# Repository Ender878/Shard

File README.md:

# Shard - Custom ESP32 S3 Board :electron:

**Shard** is an open source **ESP32 S3** board that I designed as a summer project to learn more about electronics and PCB design.

## Core features:

- 16MB Flash
- WiFi and Bluethoot capabilities
- Built-in Neopixel RGB LED
- 21 configurable GPIO pins
- Up to 16V for external Power supply
- UART & Configurable SPI and I2C pins

The board itself is pretty small, 4.6x4.8cm and doesn't have mounting holes unfortunately. It is designed to be an all-feature development board for prototyping.

## Programming

### Uploading

The board doesn't come with a **USB-UART bridge**, so the firmware uploading requires user input:

- When the uploading process starts, hold the **RESET** button
- Immediately after you pressed it, press the **BOOT** button and then release the **RESET** button
- After the code is uploaded, press the **RESET** button again to exit Download Mode, so that the board can execute the code.

### Programming with Arduino IDE 2

To program this board with the **Arduino IDE**, you have to:
- Install the "esp32" board manager.
- then select the **UM-PROS3** board 
- when uploading, follow the steps listed in the **[Uploading](#uploading)** section.

### Programming with PlatformIO (recommended)

To program this board with **PlatformIO**, you should configure the **platformio.ini** file as follows:

~~~ini
[env:esp32-s3-devkitc-1]
platform = espressif32
board = shard
framework = arduino
~~~

I made a custom **board** config file for PlatformIO that specifies all the board's specifications. To use it, create a folder called **boards** and copy [this file](./shard.json) under it.

Also, this is the partition I used:

~~~csv
# Name,   Type, SubType, Offset,  Size, Flags
nvs,      data, nvs,     0x9000,  0x5000,
otadata,  data, ota,     0xe000,  0x2000,
app0,     app,  ota_0,   0x10000, 0x700000,
app1,     app,  ota_1,   0x710000,0x700000,
spiffs,   data, spiffs,  0xe10000,0x1F0000,
~~~

PlatformIO should find the board automatically. When uploading, still follow the steps in the **[Uploading](#uploading)** section.

## Reference

To design this board, I mainly referred to the Espressif's [ESP32-S3 Hardware Design Guidelines](https://docs.espressif.com/projects/esp-hardware-design-guidelines/en/latest/esp32s3/esp-hardware-design-guidelines-en-master-esp32s3.pdf).

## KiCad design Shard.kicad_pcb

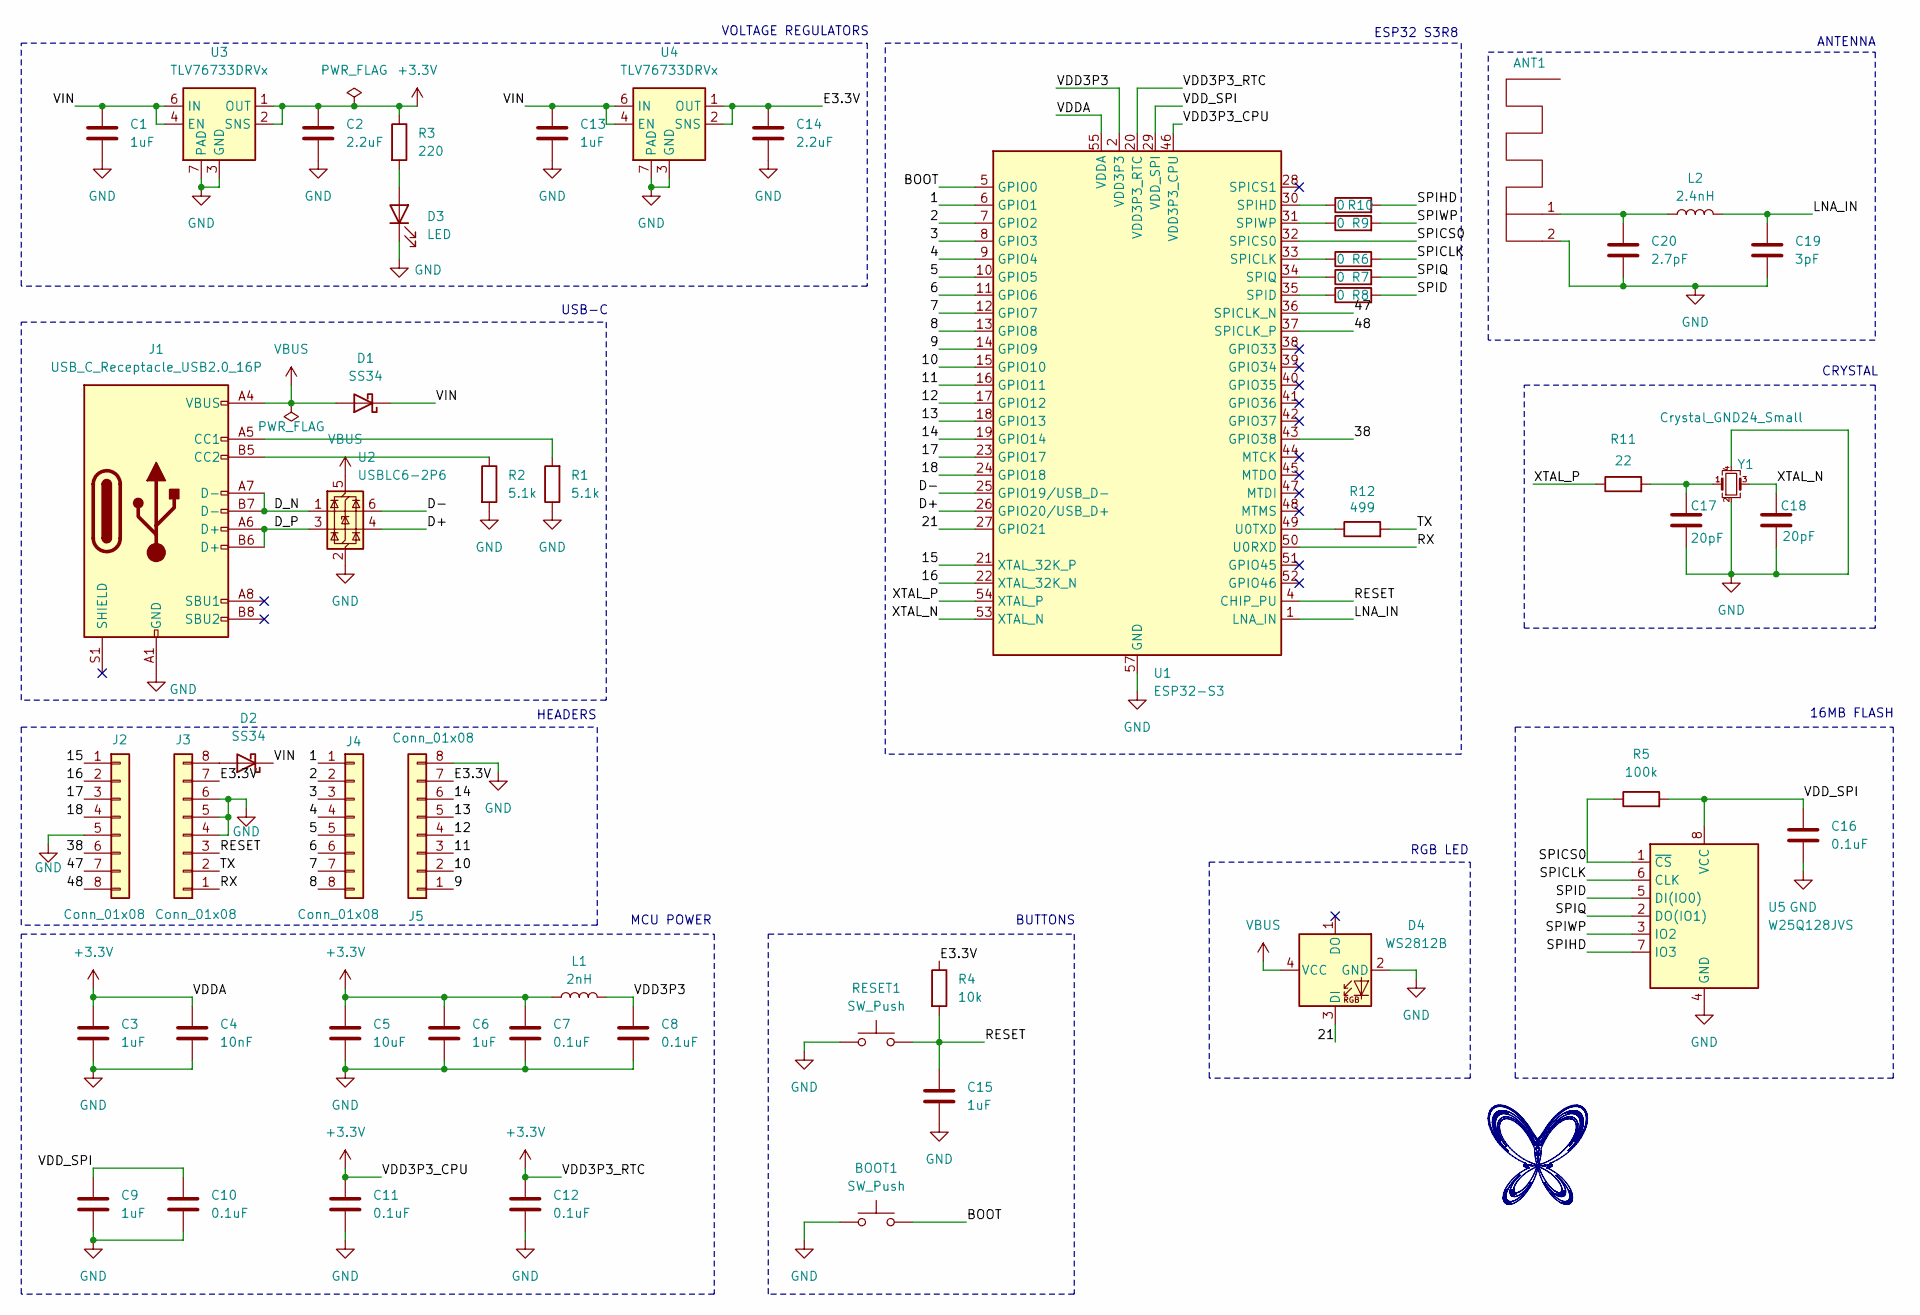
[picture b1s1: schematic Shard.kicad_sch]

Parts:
ANT1: Texas_SWRA117D_2.4GHz_Right
BOOT1: SW_Push; SW_Push_SPST_NO_Alps_SKRK
C1, C3, C9, C13, C15: 1uF; C_0201_0603Metric
C2, C14: 2.2uF; C_0402_1005Metric
C4: 10nF; C_0201_0603Metric
C5: 10uF; C_0805_2012Metric
C6: 1uF; C_0402_1005Metric
C7, C8: 0.1uF; C_0402_1005Metric
C10, C11, C12, C16: 0.1uF; C_0201_0603Metric
C17, C18: 20pF; C_0201_0603Metric
C19: 3pF; C_0201_0603Metric
C20: 2.7pF; C_0402_1005Metric
D1, D2: SS34; D_SMA
D3: LED; LED_0805_2012Metric
D4: WS2812B; LED_WS2812B-2020_PLCC4_2.0x2.0mm
J1: USB_C_Receptacle_USB2.0_16P; USB_C_Receptacle_GCT_USB4105-xx-A_16P_TopMnt_Horizontal
J2, J3, J4, J5: Conn_01x08; PinSocket_1x08_P2.54mm_Vertical
L1: 2nH; L_0201_0603Metric
L2: 2.4nH; L_0201_0603Metric
R1, R2: 5.1k; R_0402_1005Metric
R3: 220; R_0805_2012Metric
R4: 10k; R_0402_1005Metric
R5: 100k; R_1210_3225Metric
R6, R7, R8, R9, R10: 0; R_0201_0603Metric
R11: 22; R_0201_0603Metric
R12: 499; R_0805_2012Metric
RESET1: SW_Push; SW_Push_SPST_NO_Alps_SKRK
U1: ESP32-S3; QFN-56-1EP_7x7mm_P0.4mm_EP4x4mm
U2: USBLC6-2P6; SOT-666
U3, U4: TLV76733DRVx; WSON-6-1EP_2x2mm_P0.65mm_EP1x1.6mm_ThermalVias
U5: W25Q128JVS; SOIC-8_5.23x5.23mm_P1.27mm
Y1: Crystal_GND24_Small; Crystal_SMD_2520-4Pin_2.5x2.0mm

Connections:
+3.3V: C2.1, C3.1, C4.1, C5.1, C6.1, C7.1, C11.1, C12.1, L1.1, R3.1, U1.20 (VDD3P3_RTC), U1.46 (VDD3P3_CPU), U1.55 (VDDA), U1.56 (VDDA), U3.1 (OUT), U3.2 (SNS)
/1: J4.1, U1.6 (GPIO1)
/2: J4.2, U1.7 (GPIO2)
/3: J4.3, U1.8 (GPIO3)
/4: J4.4, U1.9 (GPIO4)
/5: J4.5, U1.10 (GPIO5)
/6: J4.6, U1.11 (GPIO6)
/7: J4.7, U1.12 (GPIO7)
/8: J4.8, U1.13 (GPIO8)
/9: J5.1, U1.14 (GPIO9)
/10: J5.2, U1.15 (GPIO10)
/11: J5.3, U1.16 (GPIO11)
/12: J5.4, U1.17 (GPIO12)
/13: J5.5, U1.18 (GPIO13)
/14: J5.6, U1.19 (GPIO14)
/15: J2.1, U1.21 (XTAL_32K_P)
/16: J2.2, U1.22 (XTAL_32K_N)
/17: J2.3, U1.23 (GPIO17)
/18: J2.4, U1.24 (GPIO18)
/21: D4.3 (DI), U1.27 (GPIO21)
/38: J2.6, U1.43 (GPIO38)
/47: J2.7, U1.36 (SPICLK_N)
/48: J2.8, U1.37 (SPICLK_P)
/BOOT: BOOT1.2, U1.5 (GPIO0); also elsewhere on the board
/D+: U1.26 (GPIO20/USB_D+), U2.4 (I/O2)
/D-: U1.25 (GPIO19/USB_D-), U2.6 (I/O1)
/D_N: J1.A7 (D-), J1.B7 (D-), U2.1 (I/O1)
/D_P: J1.A6 (D+), J1.B6 (D+), U2.3 (I/O2)
/E3.3V: C14.1, J3.7, J5.7, R4.1, U4.1 (OUT), U4.2 (SNS)
/LNA_IN: C19.1, L2.2, U1.1 (LNA_IN)
/RESET: C15.1, J3.3, R4.2, RESET1.2, U1.4 (CHIP_PU); also elsewhere on the board
/RX: J3.1, U1.50 (U0RXD)
/SPICLK: R6.2, U5.6 (CLK)
/SPICS0: R5.1, U1.32 (SPICS0), U5.1 (~CS)
/SPID: R8.2, U5.5 (DI(IO0))
/SPIHD: R10.2, U5.7 (IO3)
/SPIQ: R7.2, U5.2 (DO(IO1))
/SPIWP: R9.2, U5.3 (IO2)
/TX: J3.2, R12.2
/VDD3P3: C8.1, L1.2, U1.2 (VDD3P3), U1.3 (VDD3P3)
/VDD_SPI: C9.1, C10.1, C16.1, R5.2, U1.29 (VDD_SPI), U5.8 (VCC)
/VIN: C1.1, C13.1, D1.1 (K), D2.1 (K), U3.4 (EN), U3.6 (IN), U4.4 (EN), U4.6 (IN)
/XTAL_N: C18.1, U1.53 (XTAL_N), Y1.3
/XTAL_P: R11.1, U1.54 (XTAL_P)
GND: ANT1.2, BOOT1.1, C1.2, C2.2, C3.2, C4.2, C5.2, C6.2, C7.2, C8.2, C9.2, C10.2, C11.2, C12.2, C13.2, C14.2, C15.2, C16.2, C17.2, C18.2, C19.2, C20.2, D3.1 (K), D4.2 (GND), J1.A1 (GND), J1.A12 (GND), J1.B1 (GND), J1.B12 (GND), J2.5, J3.4, J3.5, J3.6, J5.8, R1.1, R2.2, RESET1.1, U1.57 (GND), U2.2 (GND), U3.3 (GND), U3.5 (GND), U3.7 (PAD), U4.3 (GND), U4.5 (GND), U4.7 (PAD), U5.4 (GND), Y1.2, Y1.4; also elsewhere on the board
unnamed: ANT1.1, C20.1, L2.1
unnamed: C17.1, R11.2, Y1.1
unnamed: D2.2 (A), J3.8
unnamed: D3.2 (A), R3.2
unnamed: J1.A5 (CC1), R1.2
unnamed: J1.B5 (CC2), R2.1
unnamed: R6.1, U1.33 (SPICLK)
unnamed: R8.1, U1.35 (SPID)
unnamed: R10.1, U1.30 (SPIHD)
unnamed: R7.1, U1.34 (SPIQ)
unnamed: R9.1, U1.31 (SPIWP)
unnamed: R12.1, U1.49 (U0TXD)
VBUS: D1.2 (A), D4.4 (VCC), J1.A4 (VBUS), J1.A9 (VBUS), J1.B4 (VBUS), J1.B9 (VBUS), U2.5 (VBUS)

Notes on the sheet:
CRYSTAL
HEADERS
MCU POWER
16MB FLASH
ANTENNA
USB-C
RGB LED
ESP32 S3R8
BUTTONS
VOLTAGE REGULATORS

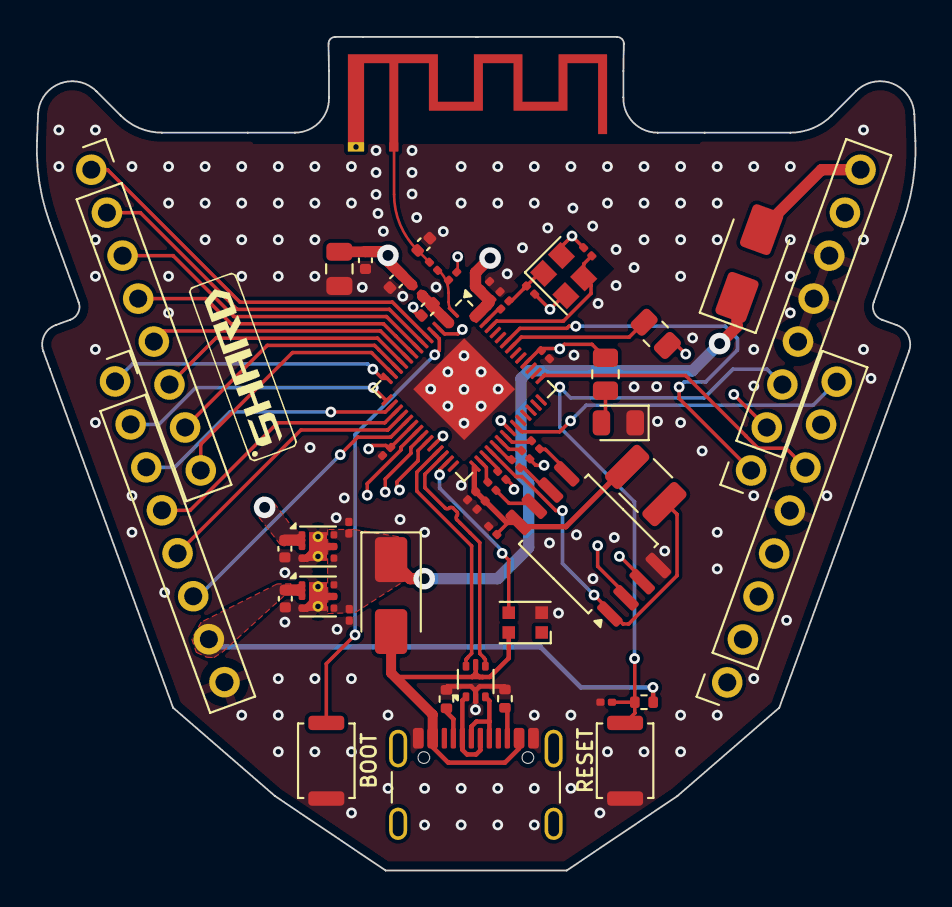
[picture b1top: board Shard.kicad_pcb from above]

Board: 4 copper layers, 48.8 x 46.3 mm, 52 parts (0 on the bottom side), 58 nets.

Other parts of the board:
BOOT: SW_Push; SW_Push_SPST_NO_Alps_SKRK
RESET: SW_Push; SW_Push_SPST_NO_Alps_SKRK

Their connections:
/BOOT: BOOT.2; also elsewhere on the board
/RESET: RESET.2; also elsewhere on the board
GND: BOOT.1, RESET.1; also elsewhere on the board

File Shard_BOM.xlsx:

Comment | Designator | Footprint | JLCPCB Part #（optional）
~ | ANT1 | RF_Antenna:Texas_SWRA117D_2.4GHz_Right
1uF | C1 | Capacitor_SMD:C_0201_0603Metric | C5209398
2.2uF | C2 | Capacitor_SMD:C_0402_1005Metric | C386078
1uF | C3 | Capacitor_SMD:C_0201_0603Metric | C5209398
10nF | C4 | Capacitor_SMD:C_0201_0603Metric | C312126
10uF | C5 | Capacitor_SMD:C_0805_2012Metric | C100083
1uF | C6 | Capacitor_SMD:C_0402_1005Metric | C325464
0.1uF | C7 | Capacitor_SMD:C_0402_1005Metric | C312123
0.1uF | C8 | Capacitor_SMD:C_0402_1005Metric | C312123
1uF | C9 | Capacitor_SMD:C_0201_0603Metric | C5209398
0.1uF | C10 | Capacitor_SMD:C_0201_0603Metric | C312124
0.1uF | C11 | Capacitor_SMD:C_0201_0603Metric | C312124
0.1uF | C12 | Capacitor_SMD:C_0201_0603Metric | C312124
1uF | C13 | Capacitor_SMD:C_0201_0603Metric | C5209398
2.2uF | C14 | Capacitor_SMD:C_0402_1005Metric | C386078
1uF | C15 | Capacitor_SMD:C_0201_0603Metric | C5209398
0.1uF | C16 | Capacitor_SMD:C_0201_0603Metric | C312124
20pF | C17 | Capacitor_SMD:C_0201_0603Metric | C426053
20pF | C18 | Capacitor_SMD:C_0201_0603Metric | C426053
3pF | C19 | Capacitor_SMD:C_0201_0603Metric | C508850
2.7pF | C20 | Capacitor_SMD:C_0402_1005Metric | C386137
SS34 | D1 | Diode_SMD:D_SMA | C8678
SS34 | D2 | Diode_SMD:D_SMA | C8678
LED | D3 | LED_SMD:LED_0805_2012Metric | C2297
WS2812B | D4 | LED_SMD:LED_WS2812B-2020_PLCC4_2.0x2.0mm | C965555
USB_C_Receptacle_USB2.0_16P | J1 | Connector_USB:USB_C_Receptacle_GCT_USB4105-xx-A_16P_TopMnt_Horizontal | C2927038
Conn_01x08 | J2 | Connector_PinSocket_2.54mm:PinSocket_1x08_P2.54mm_Vertical
Conn_01x08 | J3 | Connector_PinSocket_2.54mm:PinSocket_1x08_P2.54mm_Vertical
Conn_01x08 | J4 | Connector_PinSocket_2.54mm:PinSocket_1x08_P2.54mm_Vertical
Conn_01x08 | J5 | Connector_PinSocket_2.54mm:PinSocket_1x08_P2.54mm_Vertical
2nH | L1 | Inductor_SMD:L_0201_0603Metric | C415347
2.4nH | L2 | Inductor_SMD:L_0201_0603Metric | C87200
5.1k | R1 | Resistor_SMD:R_0402_1005Metric | C294638
5.1k | R2 | Resistor_SMD:R_0402_1005Metric | C294638
220 | R3 | Resistor_SMD:R_0805_2012Metric | C2771036
10k | R4 | Resistor_SMD:R_0402_1005Metric | C3152101
100k | R5 | Resistor_SMD:R_1210_3225Metric | C304940
0 | R6 | Resistor_SMD:R_0201_0603Metric | C965347
0 | R7 | Resistor_SMD:R_0201_0603Metric | C965347
0 | R8 | Resistor_SMD:R_0201_0603Metric | C965347
0 | R9 | Resistor_SMD:R_0201_0603Metric | C965347
0 | R10 | Resistor_SMD:R_0201_0603Metric | C965347
22 | R11 | Resistor_SMD:R_0201_0603Metric | C306975
499 | R12 | Resistor_SMD:R_0805_2012Metric | C17722
BOOT | BOOT | Button_Switch_SMD:SW_Push_SPST_NO_Alps_SKRK | C720477
RESET | RESET | Button_Switch_SMD:SW_Push_SPST_NO_Alps_SKRK | C720477
ESP32-S3 | U1 | Package_DFN_QFN:QFN-56-1EP_7x7mm_P0.4mm_EP4x4mm | C2913194
USBLC6-2P6 | U2 | Package_TO_SOT_SMD:SOT-666 | C2827693
TLV76733DRVx | U3 | Package_SON:WSON-6-1EP_2x2mm_P0.65mm_EP1x1.6mm_ThermalVias | C2848334
TLV76733DRVx | U4 | Package_SON:WSON-6-1EP_2x2mm_P0.65mm_EP1x1.6mm_ThermalVias | C2848334
W25Q128JVS | U5 | Package_SO:SOIC-8_5.23x5.23mm_P1.27mm | C97521
40Mhz | Y1 | Crystal:Crystal_SMD_2520-4Pin_2.5x2.0mm | C409423

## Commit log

2024-06-30 Add USB & ESP32 S3 symbols + initial usb wiring.
2024-06-30 USB-C Wiring
2024-06-30 Add voltage regulator
2024-06-30 Add battery connector
2024-06-30 Add missing footprint and parts
2024-07-01 Add MCU power schematic + Footprint and part assignation
2024-07-01 Add missing inductor footprint + LDO for external 3.3V alimentation.
2024-07-01 Add Reset & boot buttons (footprints and parts associated)
2024-07-01 Add 16MB Flash with footprint & part
2024-07-01 Add Crystal Oscillator.
2024-07-01 Finish crystal scheme, started GPIO labeling
2024-07-02 GPIO pin labeling
2024-07-02 Add RF circuit
2024-07-02 Add RF Antenna footprint
2024-07-02 Finished schematic with headers
2024-07-03 USB-C PCB routing
2024-07-04 Finish initial PCB Layout
2024-07-05 Started routing USB & Power
2024-07-06 Completed Power routing
2024-07-06 Routed SPI traces
2024-07-06 RF routing and impedence matching
2024-07-07 Routed most GPIO pins
2024-07-07 Finished routing
2024-07-07 Add PCB margin
2024-07-09 Add stitching vias, checked DRC rules
2024-07-09 Add pinout to bottom silkscreen
2024-07-10 Add production files
2024-07-12 Fixed some things
2024-08-07 Fix design errors & update README
2024-08-07 Rename Shard.pdf to Shard-schematic.pdf
